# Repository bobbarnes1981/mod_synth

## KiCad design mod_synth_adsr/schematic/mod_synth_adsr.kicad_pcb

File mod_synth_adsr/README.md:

ADSR from https://www.schmitzbits.de/adsr.html

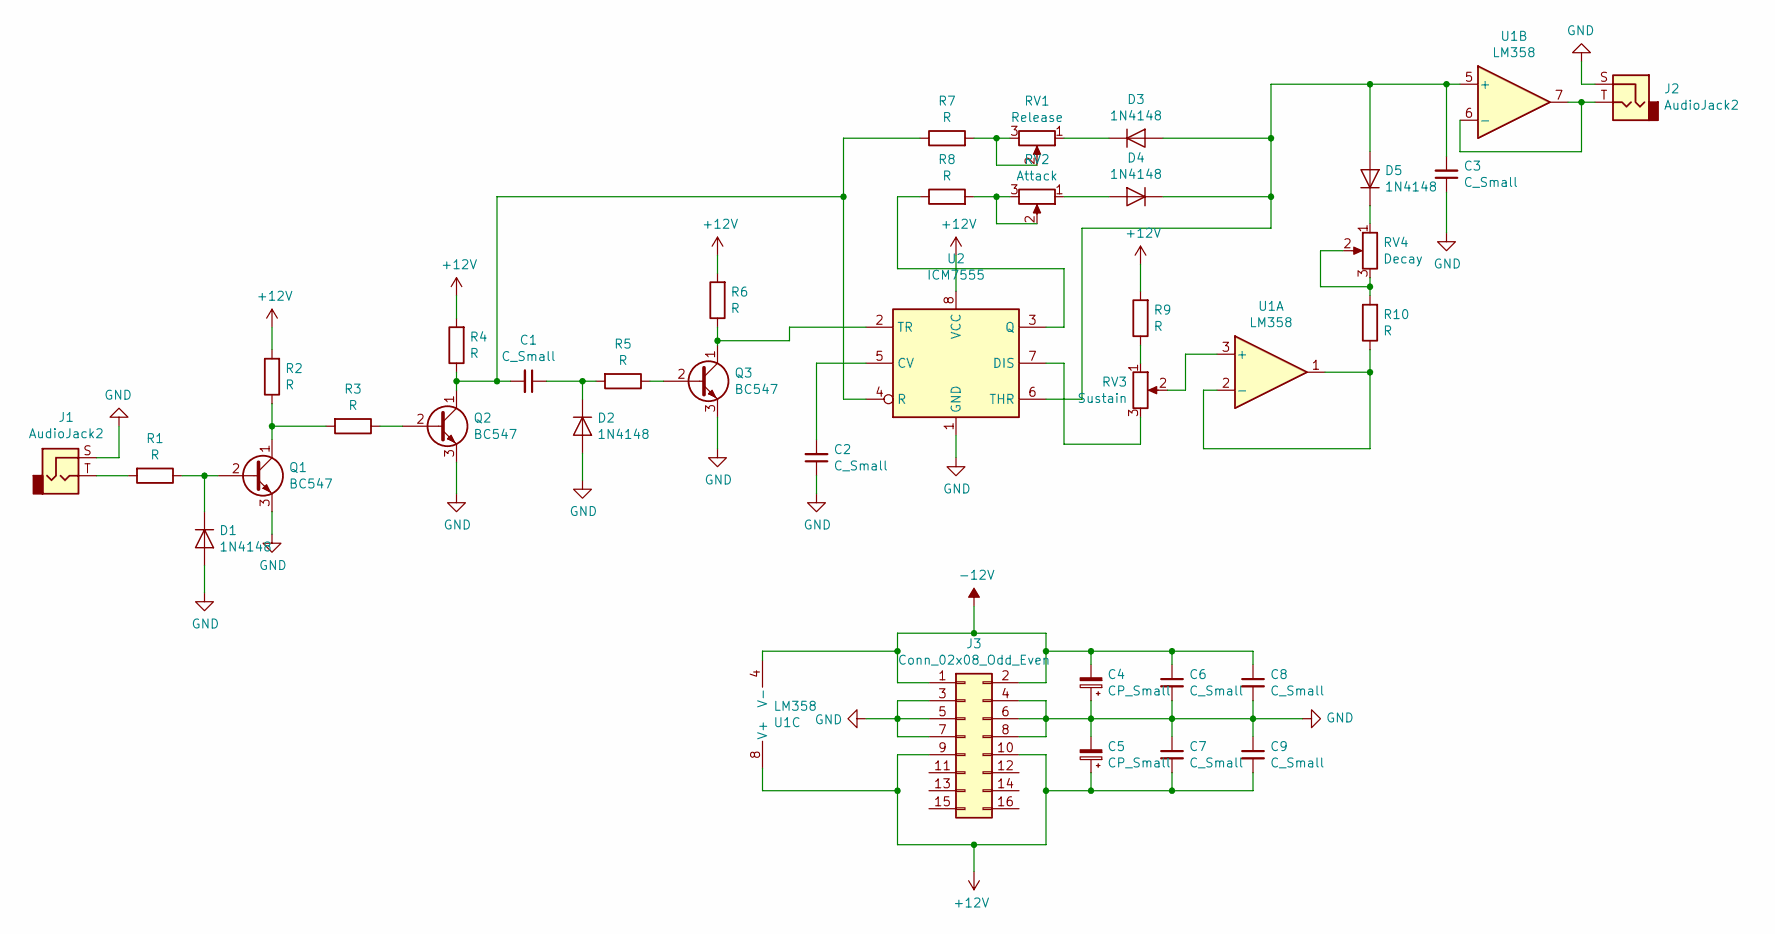
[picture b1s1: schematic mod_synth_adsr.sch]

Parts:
C1, C2, C3, C6, C7, C8, C9: C_Small; C_Disc_D9.0mm_W2.5mm_P5.00mm
C4, C5: CP_Small; CP_Radial_D5.0mm_P2.00mm
D1, D2, D3, D4, D5: 1N4148; D_DO-35_SOD27_P7.62mm_Horizontal
J1, J2: AudioJack2; Jack_3.5mm_QingPu_WQP-PJ398SM_Vertical_CircularHoles
J3: Conn_02x08_Odd_Even; IDC-Header_2x08_P2.54mm_Vertical
Q1, Q2, Q3: BC547; TO-92_Inline
R1, R2, R3, R4, R5, R6, R7, R8, R9, R10: R; R_Axial_DIN0207_L6.3mm_D2.5mm_P10.16mm_Horizontal
RV1: Release; Potentiometer_Alpha_RD901F-40-00D_Single_Vertical_CircularH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
RV2: Attack; Potentiometer_Alpha_RD901F-40-00D_Single_Vertical_CircularH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
RV3: Sustain; Potentiometer_Alpha_RD901F-40-00D_Single_Vertical_CircularH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
RV4: Decay; Potentiometer_Alpha_RD901F-40-00D_Single_Vertical_CircularH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
U1: LM358
U2: ICM7555; DIP-8_W7.62mm_Socket_LongPads

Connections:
+12V: C5.1, C7.2, C9.2, J3.9, J3.10, R2.2, R4.2, R6.2, R9.2, U1.8 (V+), U2.8 (VCC)
-12V: C4.2, C6.1, C8.1, J3.1, J3.2, U1.4 (V-)
GND: C2.1, C3.1, C4.1, C5.2, C6.2, C7.1, C8.2, C9.1, D1.2 (A), D2.2 (A), J1.S, J2.S, J3.3, J3.4, J3.5, J3.6, J3.7, J3.8, Q1.3 (E), Q2.3 (E), Q3.3 (E), U2.1 (GND)
unnamed: C1.1, D2.1 (K), R5.2
unnamed: C1.2, Q2.1 (C), R4.1, R7.1, U2.4 (R)
unnamed: C2.2, U2.5 (CV)
unnamed: C3.2, D3.2 (A), D4.1 (K), D5.2 (A), U1.5 (+), U2.6 (THR)
unnamed: D1.1 (K), Q1.2 (B), R1.1
unnamed: D3.1 (K), RV1.1
unnamed: D4.2 (A), RV2.1
unnamed: D5.1 (K), RV4.1
unnamed: J1.T, R1.2
unnamed: J2.T, U1.6 (-), U1.7
unnamed: Q1.1 (C), R2.1, R3.2
unnamed: Q2.2 (B), R3.1
unnamed: Q3.1 (C), R6.1, U2.2 (TR)
unnamed: Q3.2 (B), R5.1
unnamed: R7.2, RV1.2, RV1.3
unnamed: R8.1, U2.3 (Q)
unnamed: R8.2, RV2.2, RV2.3
unnamed: R9.1, RV3.1
unnamed: R10.1, U1.1, U1.2 (-)
unnamed: R10.2, RV4.2, RV4.3
unnamed: RV3.2, U1.3 (+)
unnamed: RV3.3, U2.7 (DIS)

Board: 2 copper layers, 36 parts (0 on the bottom side), 25 nets, no tracks yet.

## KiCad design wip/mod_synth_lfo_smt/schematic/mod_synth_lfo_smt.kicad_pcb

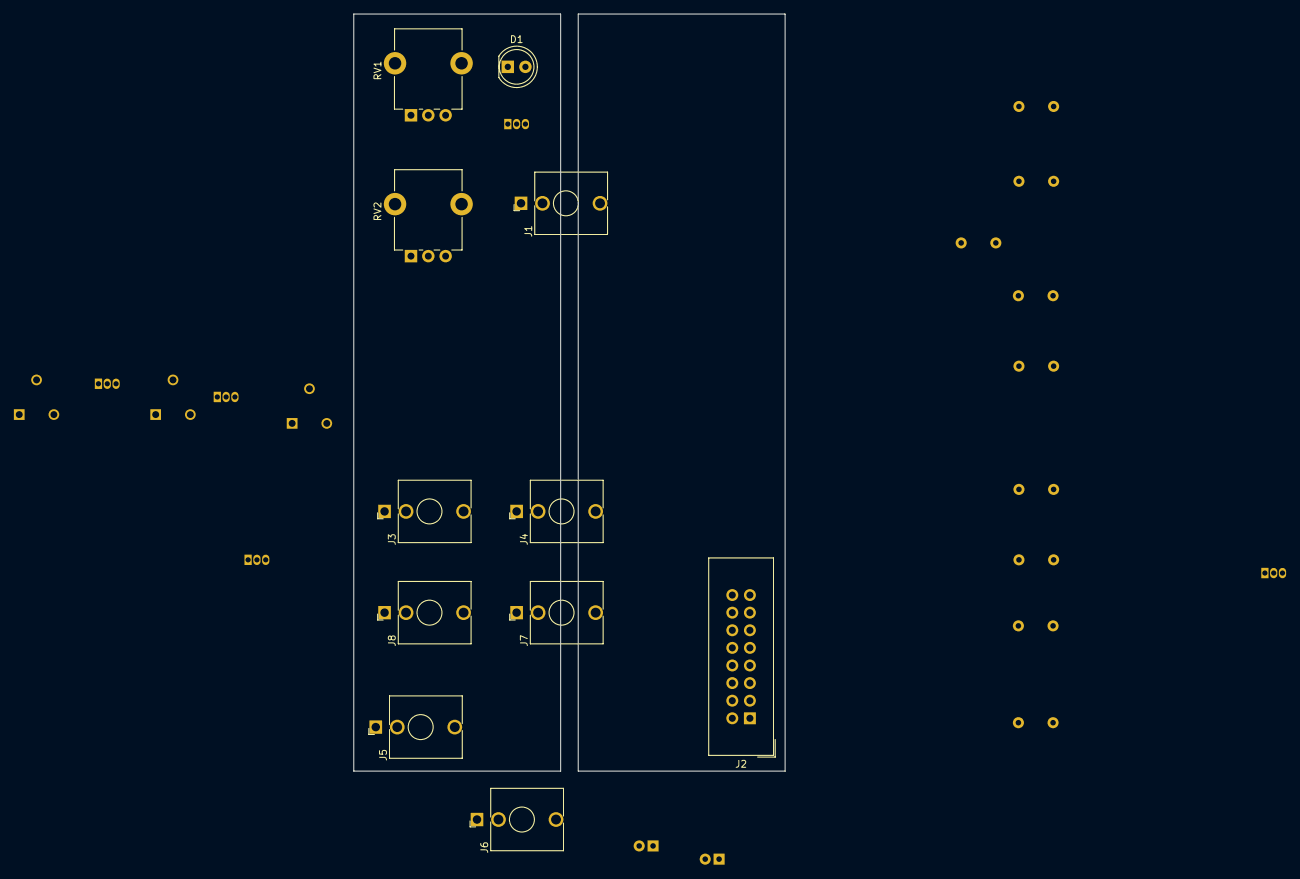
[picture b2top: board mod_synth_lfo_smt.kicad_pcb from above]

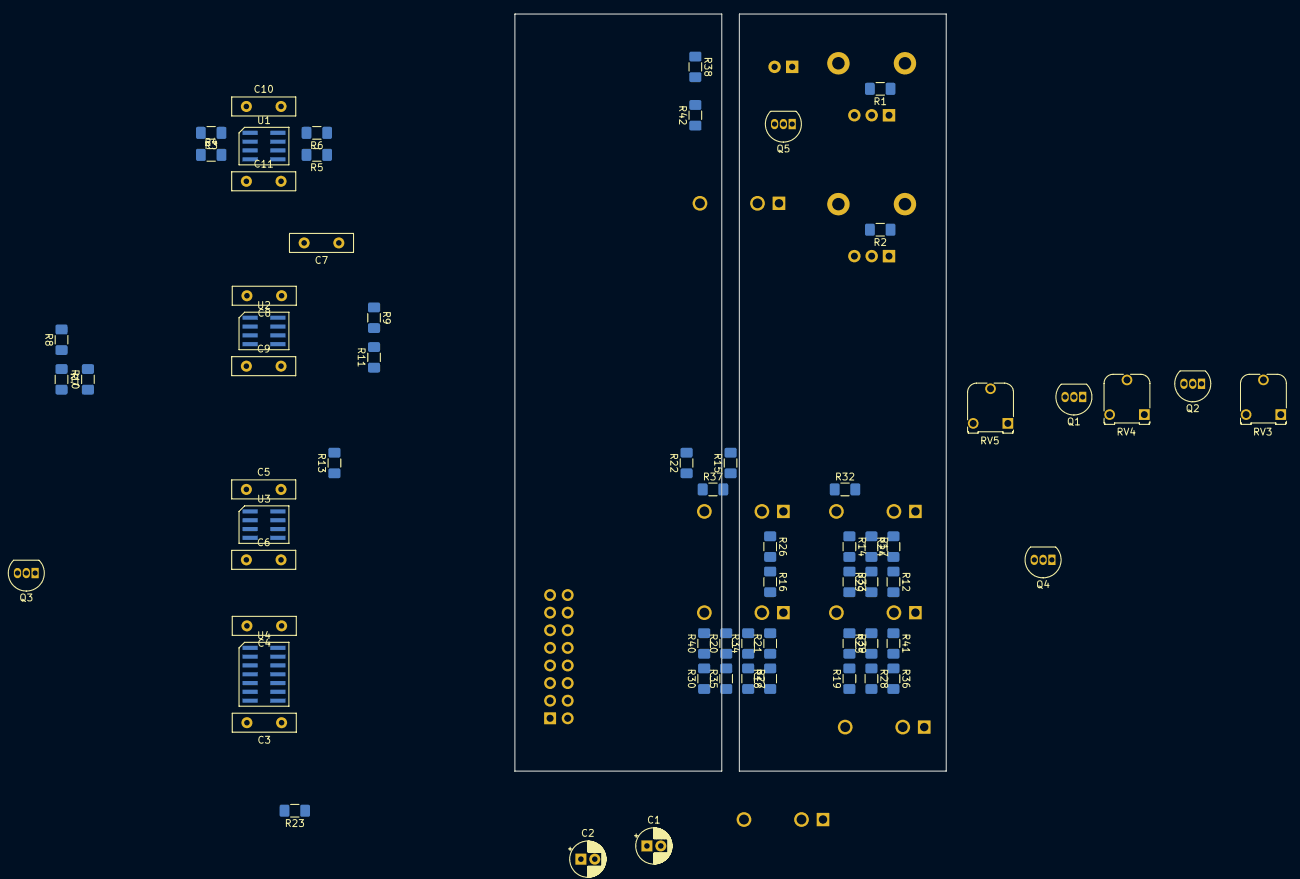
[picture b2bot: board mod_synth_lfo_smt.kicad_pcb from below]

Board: 2 copper layers, 62.2 x 109.2 mm, 75 parts (64 on the bottom side), 47 nets, no tracks yet.

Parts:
C1, C2: 10uf; CP_Radial_D5.0mm_P2.00mm
C3, C4, C5, C6, C7, C8, C9, C10, C11: 100nf; C_Disc_D9.0mm_W2.5mm_P5.00mm
D1: LED; LED_D5.0mm
J1: CV; Jack_3.5mm_QingPu_WQP-PJ398SM_Vertical_CircularHoles
J2: Conn_02x08_Odd_Even; IDC-Header_2x08_P2.54mm_Vertical
J3: SIN; Jack_3.5mm_QingPu_WQP-PJ398SM_Vertical_CircularHoles
J4: COS; Jack_3.5mm_QingPu_WQP-PJ398SM_Vertical_CircularHoles
J5: TRI; Jack_3.5mm_QingPu_WQP-PJ398SM_Vertical_CircularHoles
J6: SQR; Jack_3.5mm_QingPu_WQP-PJ398SM_Vertical_CircularHoles
J7: RAMP UP; Jack_3.5mm_QingPu_WQP-PJ398SM_Vertical_CircularHoles
J8: RAMP DOWN; Jack_3.5mm_QingPu_WQP-PJ398SM_Vertical_CircularHoles
Q1, Q2, Q3, Q4, Q5: BC550; TO-92_Inline
R1, R2, R3, R4, R5, R6, R19, R20, R21, R23, R25, R30: 100k; R_1206_3216Metric_Pad1.42x1.75mm_HandSolder
R7, R8, R9, R11, R13: 47k; R_1206_3216Metric_Pad1.42x1.75mm_HandSolder
R10, R14, R17, R18, R29, R33, R34, R35, R38, R39: 10k; R_1206_3216Metric_Pad1.42x1.75mm_HandSolder
R12, R22: 470; R_1206_3216Metric_Pad1.42x1.75mm_HandSolder
R15: 220; R_1206_3216Metric_Pad1.42x1.75mm_HandSolder
R16: 68k; R_1206_3216Metric_Pad1.42x1.75mm_HandSolder
R24, R26: 33k; R_1206_3216Metric_Pad1.42x1.75mm_HandSolder
R27: 50k; R_1206_3216Metric_Pad1.42x1.75mm_HandSolder
R28: 20k; R_1206_3216Metric_Pad1.42x1.75mm_HandSolder
R32, R36, R37, R40, R41, R42: 1k; R_1206_3216Metric_Pad1.42x1.75mm_HandSolder
RV1: SPEED; Potentiometer_Alpha_RD901F-40-00D_Single_Vertical_CircularH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
RV2: CV AMOUNT; Potentiometer_Alpha_RD901F-40-00D_Single_Vertical_CircularH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
RV3: 100k; Potentiometer_Runtron_RM-065_Vertical
RV4: 50k; Potentiometer_Runtron_RM-065_Vertical
RV5: 20k; Potentiometer_Runtron_RM-065_Vertical
U1, U2, U3: TL072; SOIC-8
U4: TL074; SOIC-14

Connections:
+12V: C1.1, C3.2, C5.2, C8.2, C10.2, D1.2, J2.9, J2.10, R14.1, R17.1, RV1.3, U1.8, U2.8, U3.8, U4.4
-12V: C2.2, C4.1, C6.1, C9.1, C11.1, J2.1, J2.2, R16.1, U1.4, U2.4, U3.4, U4.11
GND: C1.2, C2.1, C3.1, C4.2, C5.1, C6.2, C8.1, C9.2, C10.1, C11.2, J1.S, J2.3, J2.4, J2.5, J2.6, J2.7, J2.8, J3.S, J4.S, J5.S, J6.S, J7.S, J8.S, Q1.3, Q4.3, R9.1, R11.1, R12.2, R22.2, R24.2, R30.2, R42.2, RV1.1, RV2.1, RV5.2, U1.3, U1.5, U3.5, U4.12
unnamed: C7.1, R20.1, R21.1, R36.1, R38.1, RV3.1, RV3.2, U2.1, U2.6
unnamed: C7.2, R6.1, R8.2, U2.2
unnamed: D1.1, Q5.1
unnamed: J1.T, RV2.3
unnamed: J3.T, R32.1
unnamed: J4.T, R37.1
unnamed: J5.T, R36.2
unnamed: J6.T, R23.2, R30.1
unnamed: J7.T, R40.2
unnamed: J8.T, R41.1
unnamed: Q1.1, R8.1
unnamed: Q1.2, R10.1
unnamed: Q2.1, R14.2, R26.2, U3.2
unnamed: Q2.2, R12.1, RV3.3
unnamed: Q2.3, R15.2, RV4.3
unnamed: Q3.1, R17.2, R24.1, U3.3
unnamed: Q3.2, R22.1
unnamed: Q3.3, R15.1, RV4.1
unnamed: Q4.1, R21.2, U4.3
unnamed: Q4.2, R18.2
unnamed: Q5.2, R38.2
unnamed: Q5.3, R42.1
unnamed: R1.1, R2.1, R3.2, U1.2
unnamed: R1.2, RV1.2
unnamed: R2.2, RV2.2
unnamed: R3.1, R4.2, U1.1
unnamed: R4.1, R5.2, U1.6
unnamed: R5.1, R6.2, R7.2, U1.7
unnamed: R7.1, R9.2, U2.3
unnamed: R10.2, R13.2, R18.1, R19.1, R23.1, U2.7
unnamed: R11.2, R13.1, U2.5
unnamed: R16.2, RV4.2
unnamed: R19.2, U4.10
unnamed: R20.2, R25.1, U4.2
unnamed: R25.2, R28.1, U4.1
unnamed: R26.1, R29.2, R32.2, U3.1
unnamed: R27.1, RV5.1, U4.5
unnamed: R27.2, U4.8, U4.9
unnamed: R28.2, R34.1, U4.6
unnamed: R29.1, R33.2, U3.6
unnamed: R33.1, R37.2, U3.7
unnamed: R34.2, R35.1, R40.1, U4.7
unnamed: R35.2, R39.2, U4.13
unnamed: R39.1, R41.2, U4.14

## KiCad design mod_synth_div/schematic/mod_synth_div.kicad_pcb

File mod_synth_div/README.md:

Binary counter as clock divider

http://familjenronnberg.se/~niklas/diy/eurorack/divider/

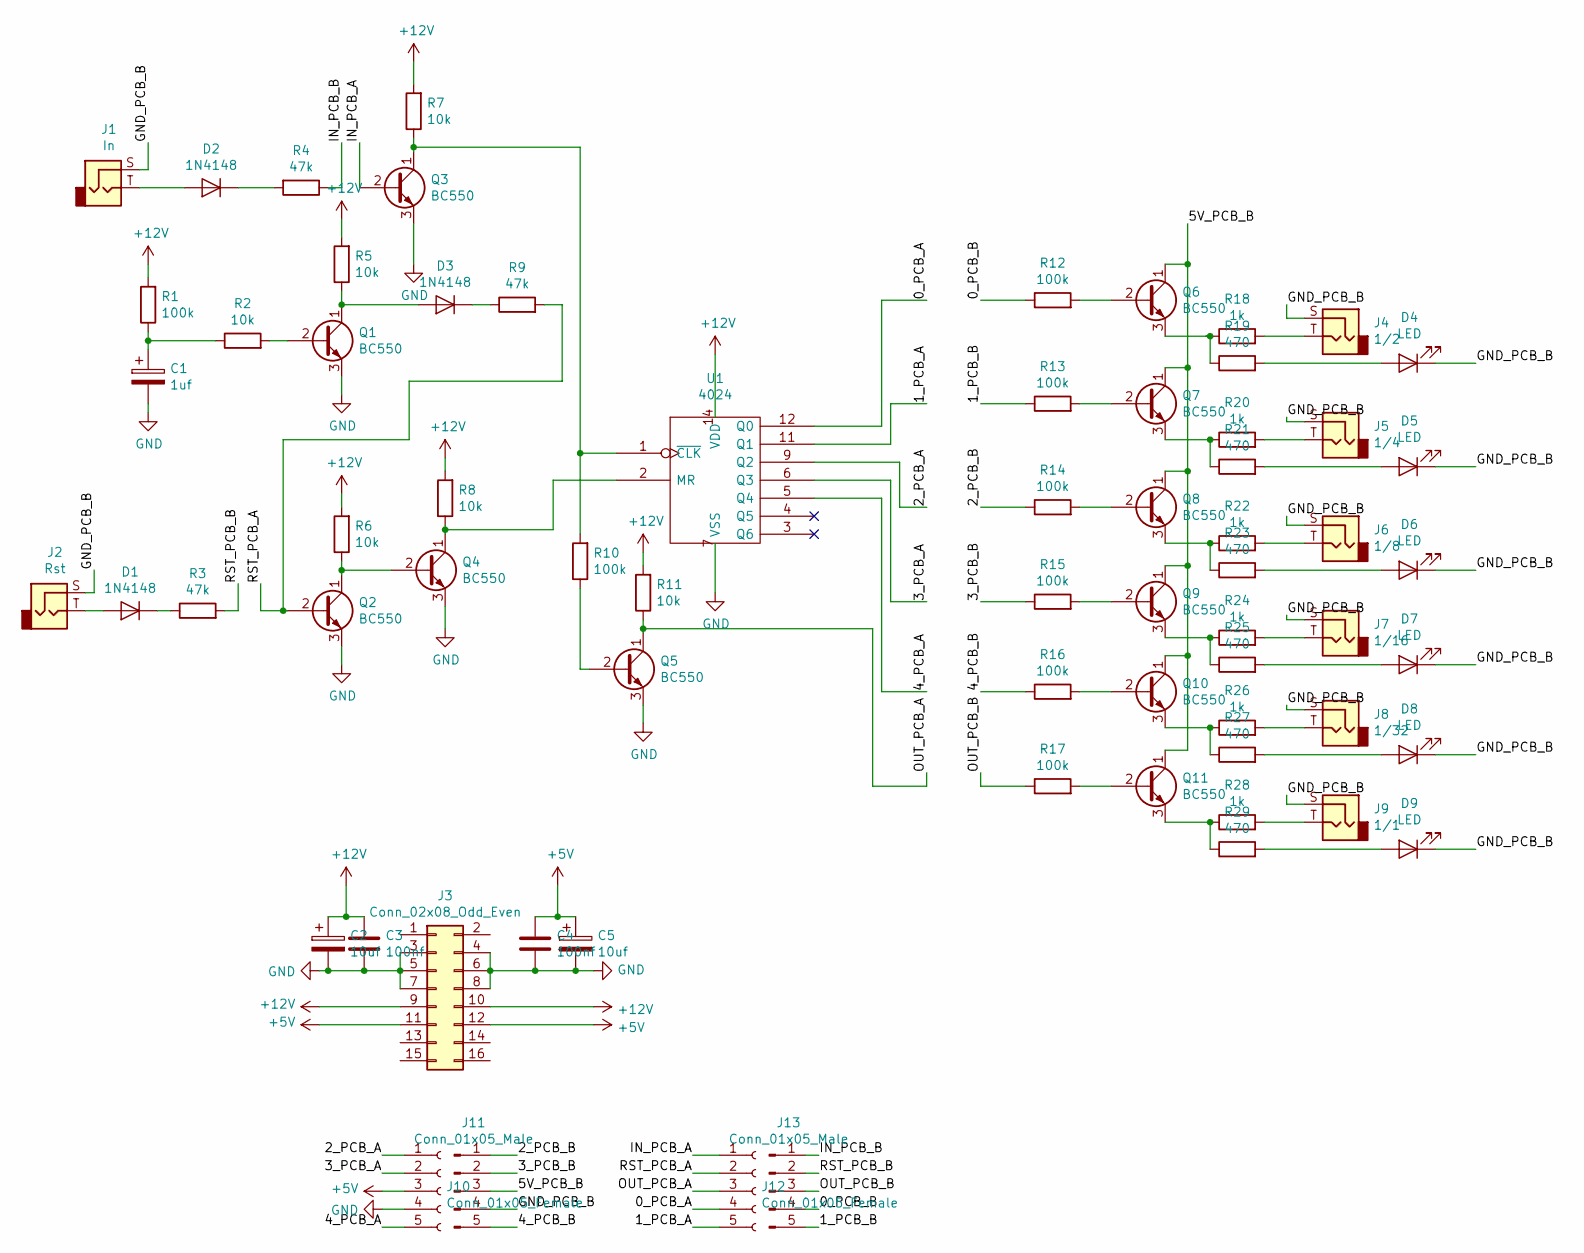
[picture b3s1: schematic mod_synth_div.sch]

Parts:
C1: 1uf; CP_Radial_D5.0mm_P2.00mm
C2, C5: 10uf; CP_Radial_D5.0mm_P2.00mm
C3, C4: 100nf; C_Disc_D9.0mm_W2.5mm_P5.00mm
D1, D2, D3: 1N4148; D_DO-35_SOD27_P7.62mm_Horizontal
D4, D5, D6, D7, D8, D9: LED; LED_D5.0mm
J1: In; Jack_3.5mm_QingPu_WQP-PJ398SM_Vertical_CircularHoles
J2: Rst; Jack_3.5mm_QingPu_WQP-PJ398SM_Vertical_CircularHoles
J3: Conn_02x08_Odd_Even; IDC-Header_2x08_P2.54mm_Vertical
J4: 1/2; Jack_3.5mm_QingPu_WQP-PJ398SM_Vertical_CircularHoles
J5: 1/4; Jack_3.5mm_QingPu_WQP-PJ398SM_Vertical_CircularHoles
J6: 1/8; Jack_3.5mm_QingPu_WQP-PJ398SM_Vertical_CircularHoles
J7: 1/16; Jack_3.5mm_QingPu_WQP-PJ398SM_Vertical_CircularHoles
J8: 1/32; Jack_3.5mm_QingPu_WQP-PJ398SM_Vertical_CircularHoles
J9: 1/1; Jack_3.5mm_QingPu_WQP-PJ398SM_Vertical_CircularHoles
J10, J12: Conn_01x05_Female; PinSocket_1x05_P2.54mm_Vertical
J11, J13: Conn_01x05_Male; PinHeader_1x05_P2.54mm_Vertical
Q1, Q2, Q3, Q4, Q5, Q6, Q7, Q8, Q9, Q10, Q11: BC550; TO-92_Inline
R1, R10, R12, R13, R14, R15, R16, R17: 100k; R_Axial_DIN0207_L6.3mm_D2.5mm_P10.16mm_Horizontal
R2, R5, R6, R7, R8, R11: 10k; R_Axial_DIN0207_L6.3mm_D2.5mm_P10.16mm_Horizontal
R3, R4, R9: 47k; R_Axial_DIN0207_L6.3mm_D2.5mm_P10.16mm_Horizontal
R18, R20, R22, R24, R26, R28: 1k; R_Axial_DIN0207_L6.3mm_D2.5mm_P10.16mm_Horizontal
R19, R21, R23, R25, R27, R29: 470; R_Axial_DIN0207_L6.3mm_D2.5mm_P10.16mm_Horizontal
U1: 4024; DIP-14_W7.62mm_Socket_LongPads

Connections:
+5V: C4.1, C5.1, J3.11, J3.12, J10.3
+12V: C2.1, C3.1, J3.9, J3.10, R1.2, R5.2, R6.2, R7.2, R8.2, R11.2, U1.14 (VDD)
/0_PCB_A: J12.4, U1.12 (Q0)
/0_PCB_B: J13.4, R12.1
/1_PCB_A: J12.5, U1.11 (Q1)
/1_PCB_B: J13.5, R13.1
/2_PCB_A: J10.1, U1.9 (Q2)
/2_PCB_B: J11.1, R14.1
/3_PCB_A: J10.2, U1.6 (Q3)
/3_PCB_B: J11.2, R15.1
/4_PCB_A: J10.5, U1.5 (Q4)
/4_PCB_B: J11.5, R16.1
/5V_PCB_B: J11.3, Q6.1 (C), Q7.1 (C), Q8.1 (C), Q9.1 (C), Q10.1 (C), Q11.1 (C)
/GND_PCB_B: D4.1 (K), D5.1 (K), D6.1 (K), D7.1 (K), D8.1 (K), D9.1 (K), J1.S, J2.S, J4.S, J5.S, J6.S, J7.S, J8.S, J9.S, J11.4
/IN_PCB_A: J12.1, Q3.2 (B)
/IN_PCB_B: J13.1, R4.1
/OUT_PCB_A: J12.3, Q5.1 (C), R11.1
/OUT_PCB_B: J13.3, R17.1
/RST_PCB_A: J12.2, Q2.2 (B), R9.2
/RST_PCB_B: J13.2, R3.2
GND: C1.2, C2.2, C3.2, C4.2, C5.2, J3.3, J3.4, J3.5, J3.6, J3.7, J3.8, J10.4, Q1.3 (E), Q2.3 (E), Q3.3 (E), Q4.3 (E), Q5.3 (E), U1.7 (VSS)
unnamed: C1.1, R1.1, R2.1
unnamed: D1.1 (K), R3.1
unnamed: D1.2 (A), J2.T
unnamed: D2.1 (K), R4.2
unnamed: D2.2 (A), J1.T
unnamed: D3.1 (K), R9.1
unnamed: D3.2 (A), Q1.1 (C), R5.1
unnamed: D4.2 (A), R19.2
unnamed: D5.2 (A), R21.2
unnamed: D6.2 (A), R23.2
unnamed: D7.2 (A), R25.2
unnamed: D8.2 (A), R27.2
unnamed: D9.2 (A), R29.2
unnamed: J4.T, R18.2
unnamed: J5.T, R20.2
unnamed: J6.T, R22.2
unnamed: J7.T, R24.2
unnamed: J8.T, R26.2
unnamed: J9.T, R28.2
unnamed: Q1.2 (B), R2.2
unnamed: Q2.1 (C), Q4.2 (B), R6.1
unnamed: Q3.1 (C), R7.1, R10.2, U1.1 (~CLK)
unnamed: Q4.1 (C), R8.1, U1.2 (MR)
unnamed: Q5.2 (B), R10.1
unnamed: Q6.2 (B), R12.2
unnamed: Q6.3 (E), R18.1, R19.1
unnamed: Q7.2 (B), R13.2
unnamed: Q7.3 (E), R20.1, R21.1
unnamed: Q8.2 (B), R14.2
unnamed: Q8.3 (E), R22.1, R23.1
unnamed: Q9.2 (B), R15.2
unnamed: Q9.3 (E), R24.1, R25.1
unnamed: Q10.2 (B), R16.2
unnamed: Q10.3 (E), R26.1, R27.1
unnamed: Q11.2 (B), R17.2
unnamed: Q11.3 (E), R28.1, R29.1

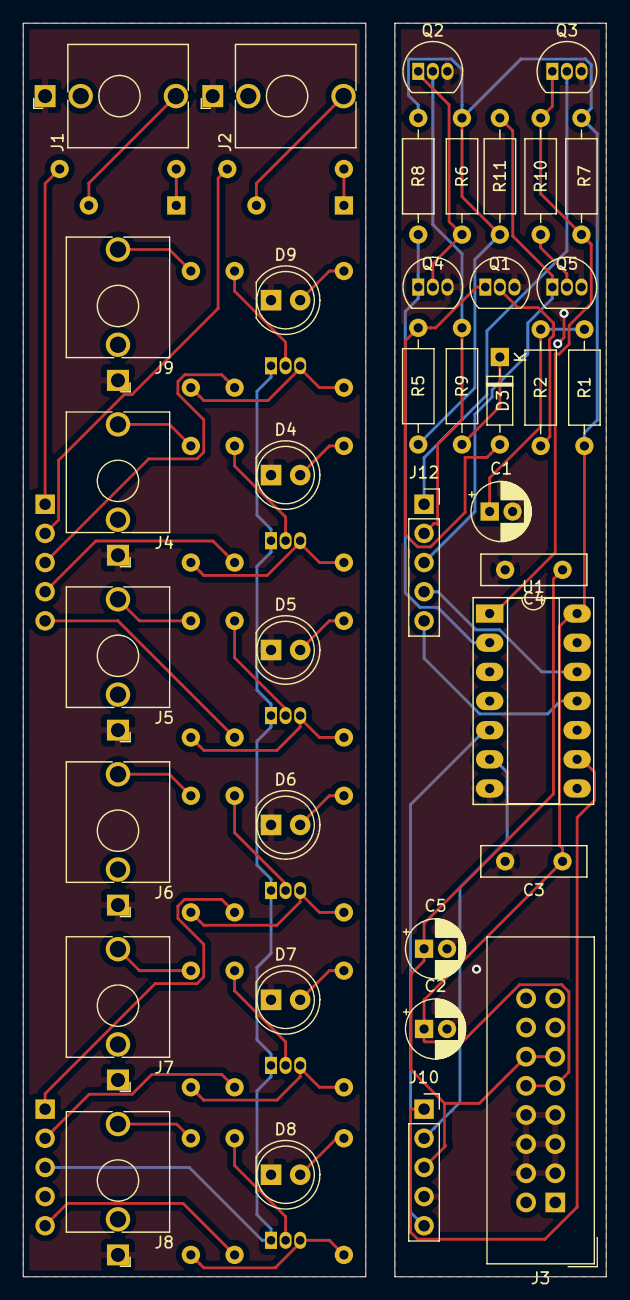
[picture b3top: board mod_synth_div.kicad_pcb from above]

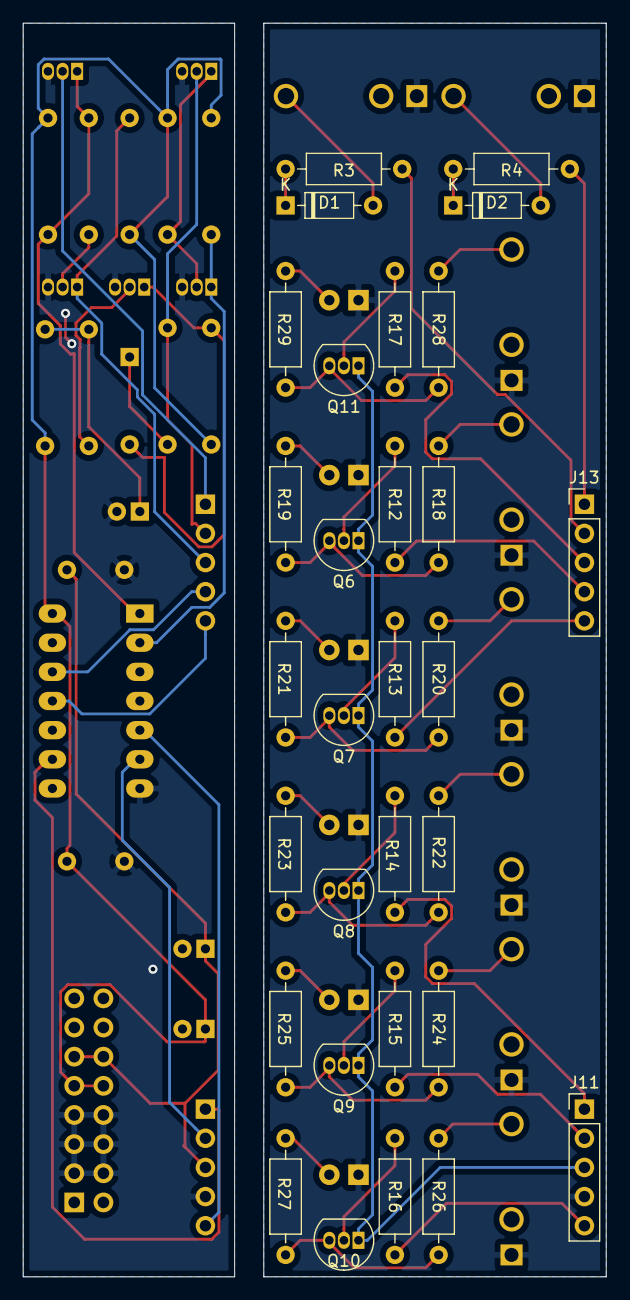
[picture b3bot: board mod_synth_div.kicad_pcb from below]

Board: 2 copper layers, 50.8 x 109.2 mm, 68 parts (30 on the bottom side), 57 nets.

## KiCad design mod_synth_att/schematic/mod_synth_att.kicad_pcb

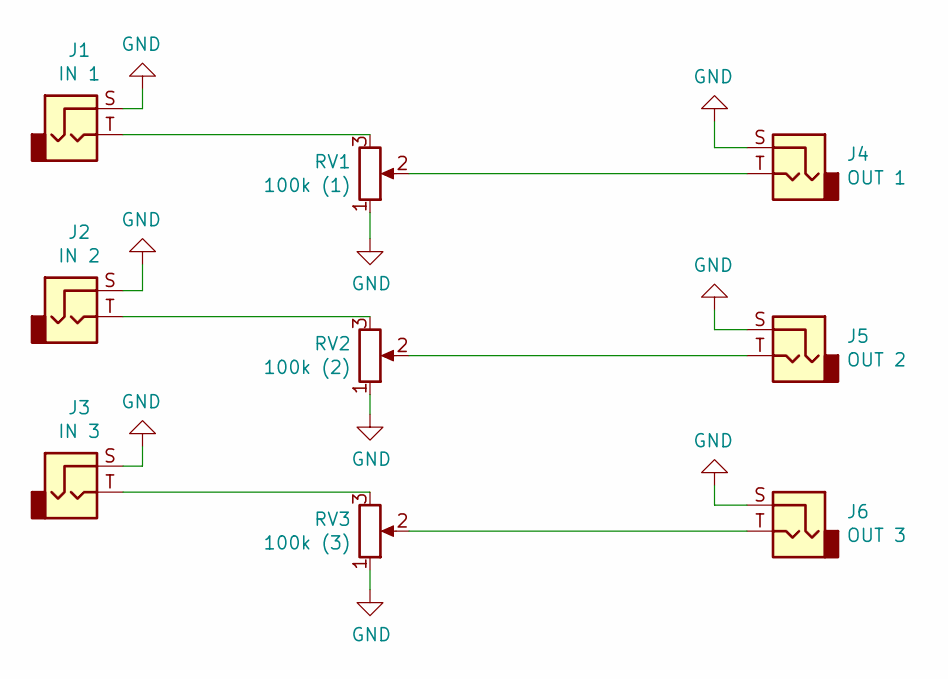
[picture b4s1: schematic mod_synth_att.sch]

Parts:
J1: IN 1; Jack_3.5mm_QingPu_WQP-PJ398SM_Vertical_CircularHoles
J2: IN 2; Jack_3.5mm_QingPu_WQP-PJ398SM_Vertical_CircularHoles
J3: IN 3; Jack_3.5mm_QingPu_WQP-PJ398SM_Vertical_CircularHoles
J4: OUT 1; Jack_3.5mm_QingPu_WQP-PJ398SM_Vertical_CircularHoles
J5: OUT 2; Jack_3.5mm_QingPu_WQP-PJ398SM_Vertical_CircularHoles
J6: OUT 3; Jack_3.5mm_QingPu_WQP-PJ398SM_Vertical_CircularHoles
RV1: 100k (1); Potentiometer_Alpha_RD901F-40-00D_Single_Vertical_CircularH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
RV2: 100k (2); Potentiometer_Alpha_RD901F-40-00D_Single_Vertical_CircularH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
RV3: 100k (3); Potentiometer_Alpha_RD901F-40-00D_Single_Vertical_CircularH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

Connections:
GND: J1.S, J2.S, J3.S, J4.S, J5.S, J6.S, RV1.1, RV2.1, RV3.1
unnamed: J1.T, RV1.3
unnamed: J2.T, RV2.3
unnamed: J3.T, RV3.3
unnamed: J4.T, RV1.2
unnamed: J5.T, RV2.2
unnamed: J6.T, RV3.2

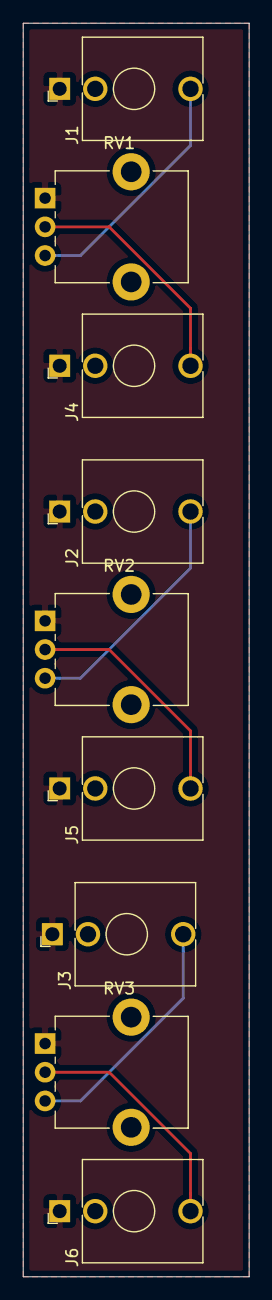
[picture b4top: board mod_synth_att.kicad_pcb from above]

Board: 2 copper layers, 19.7 x 109.2 mm, 9 parts (0 on the bottom side), 7 nets.

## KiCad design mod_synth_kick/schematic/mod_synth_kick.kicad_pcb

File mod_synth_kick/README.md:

Kick drum from

https://helsinkisoundelectronics.files.wordpress.com/2015/11/analog-bass-drum-workshop-updated.pdf

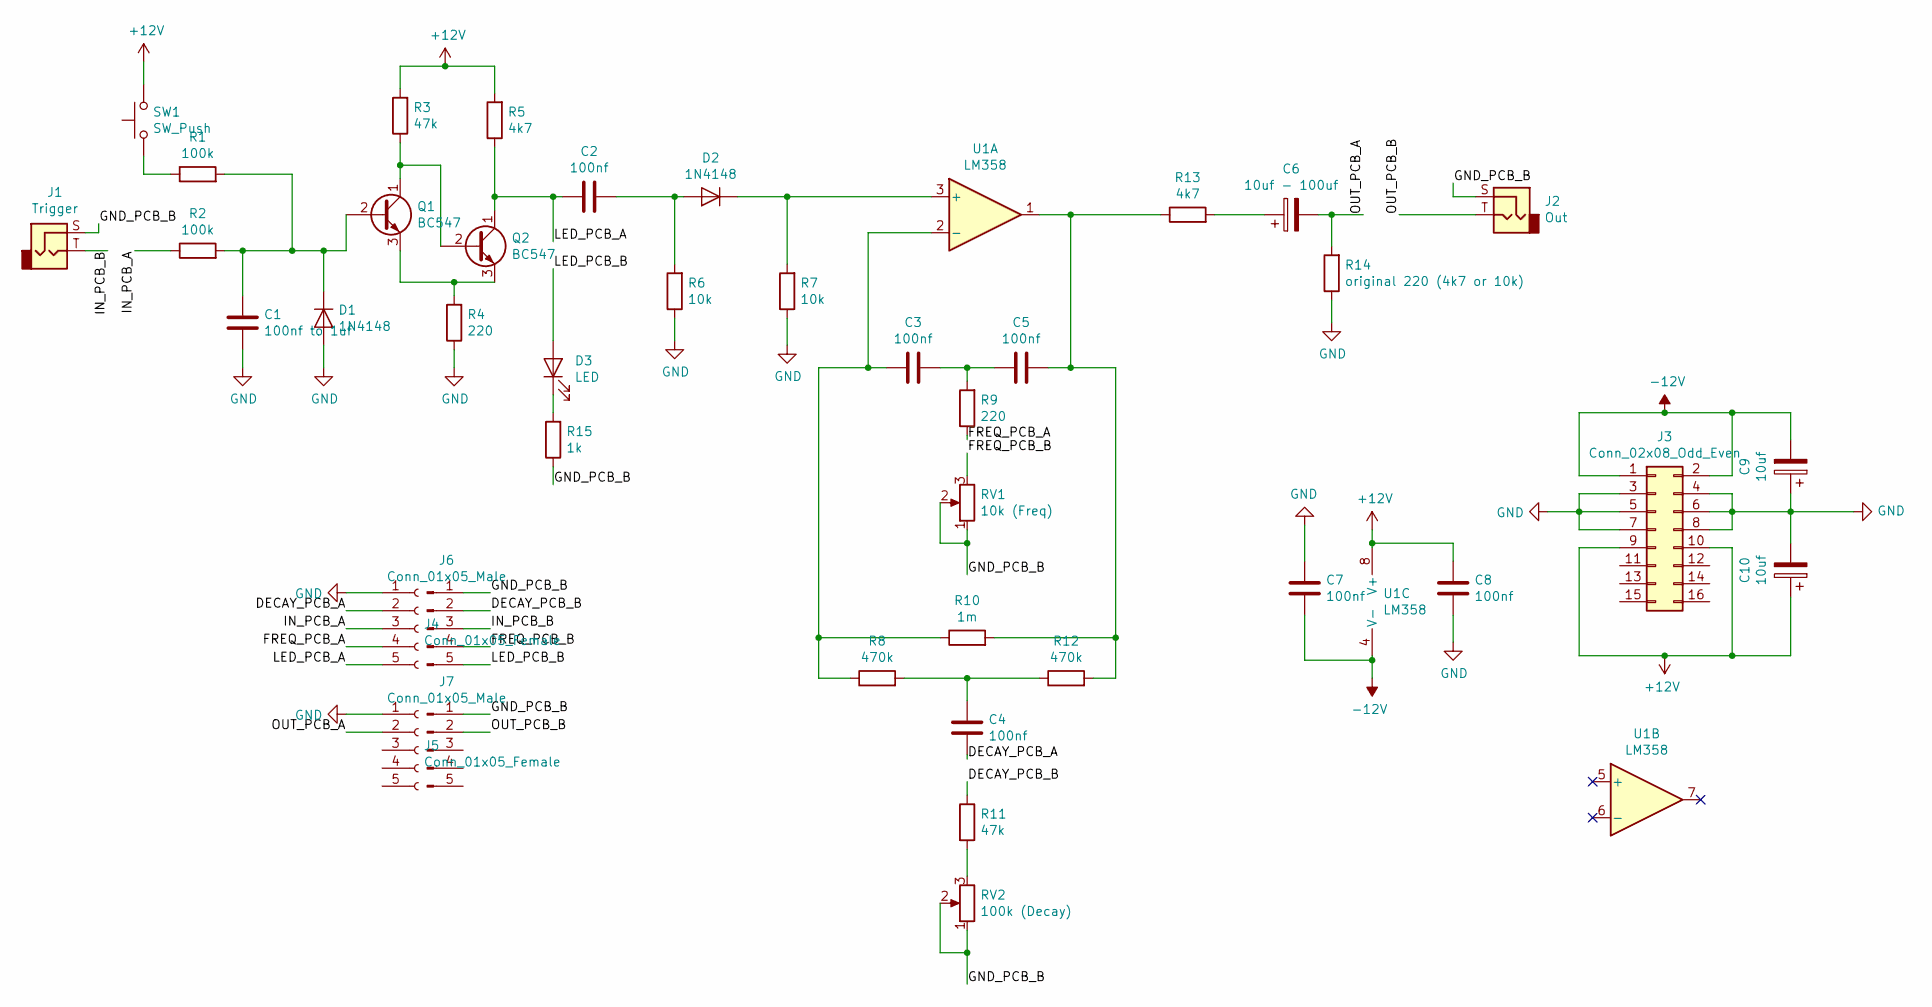
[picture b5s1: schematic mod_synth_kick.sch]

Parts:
C1: 100nf to 1uf; C_Disc_D9.0mm_W2.5mm_P5.00mm
C2, C3, C4, C5, C7, C8: 100nf; C_Disc_D9.0mm_W2.5mm_P5.00mm
C6: 10uf - 100uf; CP_Radial_D5.0mm_P2.00mm
C9, C10: 10uf; CP_Radial_D5.0mm_P2.00mm
D1, D2: 1N4148; D_DO-35_SOD27_P7.62mm_Horizontal
D3: LED; LED_D5.0mm
J1: Trigger; Jack_3.5mm_QingPu_WQP-PJ398SM_Vertical_CircularHoles
J2: Out; Jack_3.5mm_QingPu_WQP-PJ398SM_Vertical_CircularHoles
J3: Conn_02x08_Odd_Even; IDC-Header_2x08_P2.54mm_Vertical
J4, J5: Conn_01x05_Female; PinSocket_1x05_P2.54mm_Vertical
J6, J7: Conn_01x05_Male; PinHeader_1x05_P2.54mm_Vertical
Q1, Q2: BC547; TO-92_Inline
R1, R2: 100k; R_Axial_DIN0207_L6.3mm_D2.5mm_P10.16mm_Horizontal
R3, R11: 47k; R_Axial_DIN0207_L6.3mm_D2.5mm_P10.16mm_Horizontal
R4, R9: 220; R_Axial_DIN0207_L6.3mm_D2.5mm_P10.16mm_Horizontal
R5, R13: 4k7; R_Axial_DIN0207_L6.3mm_D2.5mm_P10.16mm_Horizontal
R6, R7: 10k; R_Axial_DIN0207_L6.3mm_D2.5mm_P10.16mm_Horizontal
R8, R12: 470k; R_Axial_DIN0207_L6.3mm_D2.5mm_P10.16mm_Horizontal
R10: 1m; R_Axial_DIN0207_L6.3mm_D2.5mm_P10.16mm_Horizontal
R14: original 220 (4k7 or 10k); R_Axial_DIN0207_L6.3mm_D2.5mm_P10.16mm_Horizontal
R15: 1k; R_Axial_DIN0207_L6.3mm_D2.5mm_P10.16mm_Horizontal
RV1: 10k (Freq); Potentiometer_Alpha_RD901F-40-00D_Single_Vertical_CircularH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
RV2: 100k (Decay); Potentiometer_Alpha_RD901F-40-00D_Single_Vertical_CircularH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
SW1: SW_Push; PinHeader_1x02_P2.54mm_Vertical
U1: LM358; DIP-8_W7.62mm_Socket_LongPads

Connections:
+12V: C8.2, C10.1, J3.9, J3.10, R3.2, R5.2, SW1.2, U1.8 (V+)
-12V: C7.1, C9.2, J3.1, J3.2, U1.4 (V-)
/DECAY_PCB_A: C4.2, J4.2
/DECAY_PCB_B: J6.2, R11.1
/FREQ_PCB_A: J4.4, R9.1
/FREQ_PCB_B: J6.4, RV1.3
/GND_PCB_B: J1.S, J2.S, J6.1, J7.1, R15.1, RV1.1, RV1.2, RV2.1, RV2.2
/IN_PCB_A: J4.3, R2.1
/IN_PCB_B: J1.T, J6.3
/LED_PCB_A: C2.2, J4.5, Q2.1 (C), R5.1
/LED_PCB_B: D3.2 (A), J6.5
/OUT_PCB_A: C6.2, J5.2, R14.2
/OUT_PCB_B: J2.T, J7.2
GND: C1.1, C7.2, C8.1, C9.1, C10.2, D1.2 (A), J3.3, J3.4, J3.5, J3.6, J3.7, J3.8, J4.1, J5.1, R4.1, R6.1, R7.1, R14.1
unnamed: C1.2, D1.1 (K), Q1.2 (B), R1.2, R2.2
unnamed: C2.1, D2.2 (A), R6.2
unnamed: C3.1, C5.2, R9.2
unnamed: C3.2, R8.1, R10.1, U1.2 (-)
unnamed: C4.1, R8.2, R12.1
unnamed: C5.1, R10.2, R12.2, R13.1, U1.1
unnamed: C6.1, R13.2
unnamed: D2.1 (K), R7.2, U1.3 (+)
unnamed: D3.1 (K), R15.2
unnamed: Q1.1 (C), Q2.2 (B), R3.1
unnamed: Q1.3 (E), Q2.3 (E), R4.2
unnamed: R1.1, SW1.1
unnamed: R11.2, RV2.3

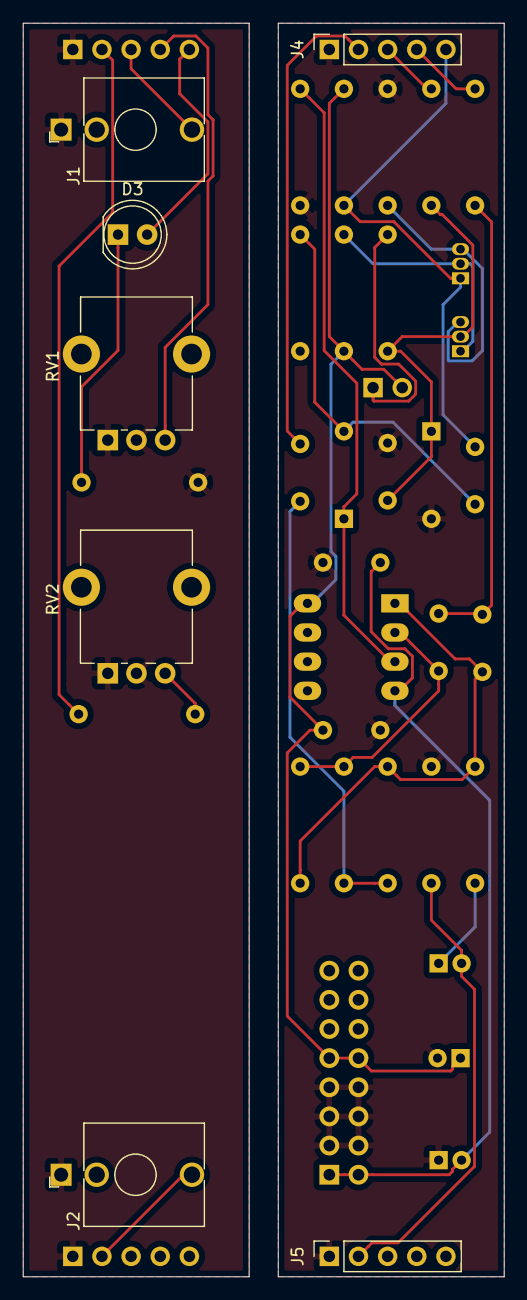
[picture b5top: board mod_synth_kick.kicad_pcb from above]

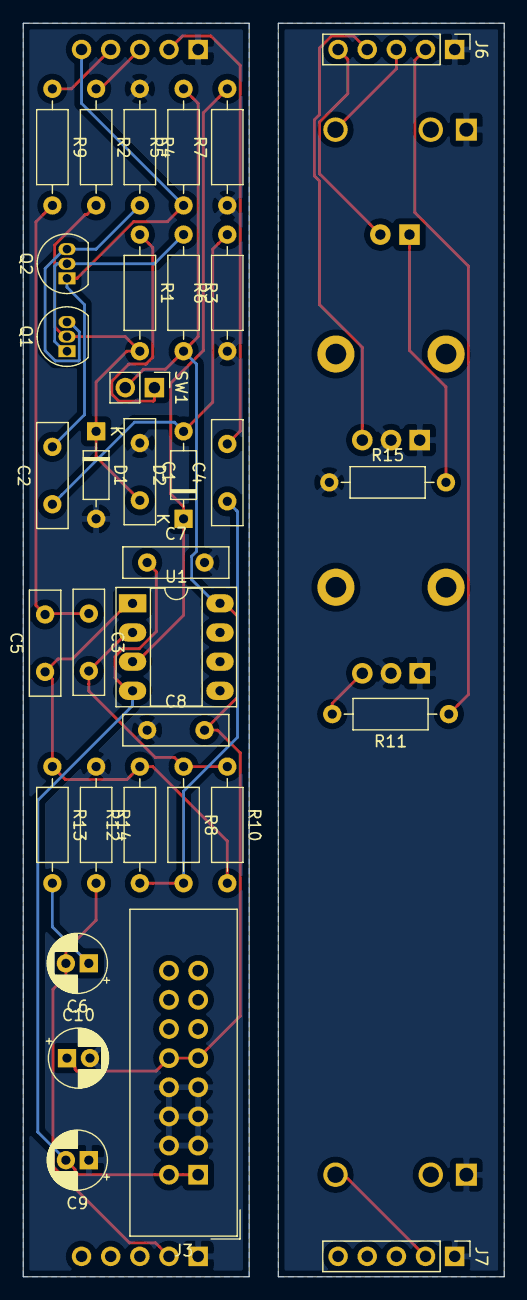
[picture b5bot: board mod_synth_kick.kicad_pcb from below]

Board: 2 copper layers, 41.9 x 109.2 mm, 41 parts (34 on the bottom side), 27 nets.
